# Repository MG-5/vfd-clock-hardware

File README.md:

# nixie-clock-hardware
Hardware for controlling six VFD IV-17 and two VFD IV-1 tubes as clock (HH:MM:SS) 

### Requirements for rev 1.0
* efficient step-boost converter up to 50V
* multiplexing
* control syncronous addressable LEDs
* PWM control
* I²C interface
* connector for ESP (UART)
* time syncronisation line for every second

### Known issues in rev 1.0
* octal buffer for PWM use seems do not works for dimming
  * workaround: dimming solved by adding turn-off points in mulitplexing routine (firmware-based solution)
* SPI is not suitable for controlling 20-bit shift register
  * cut traces and wire up to another pins

### Pictures (rev 1.0)

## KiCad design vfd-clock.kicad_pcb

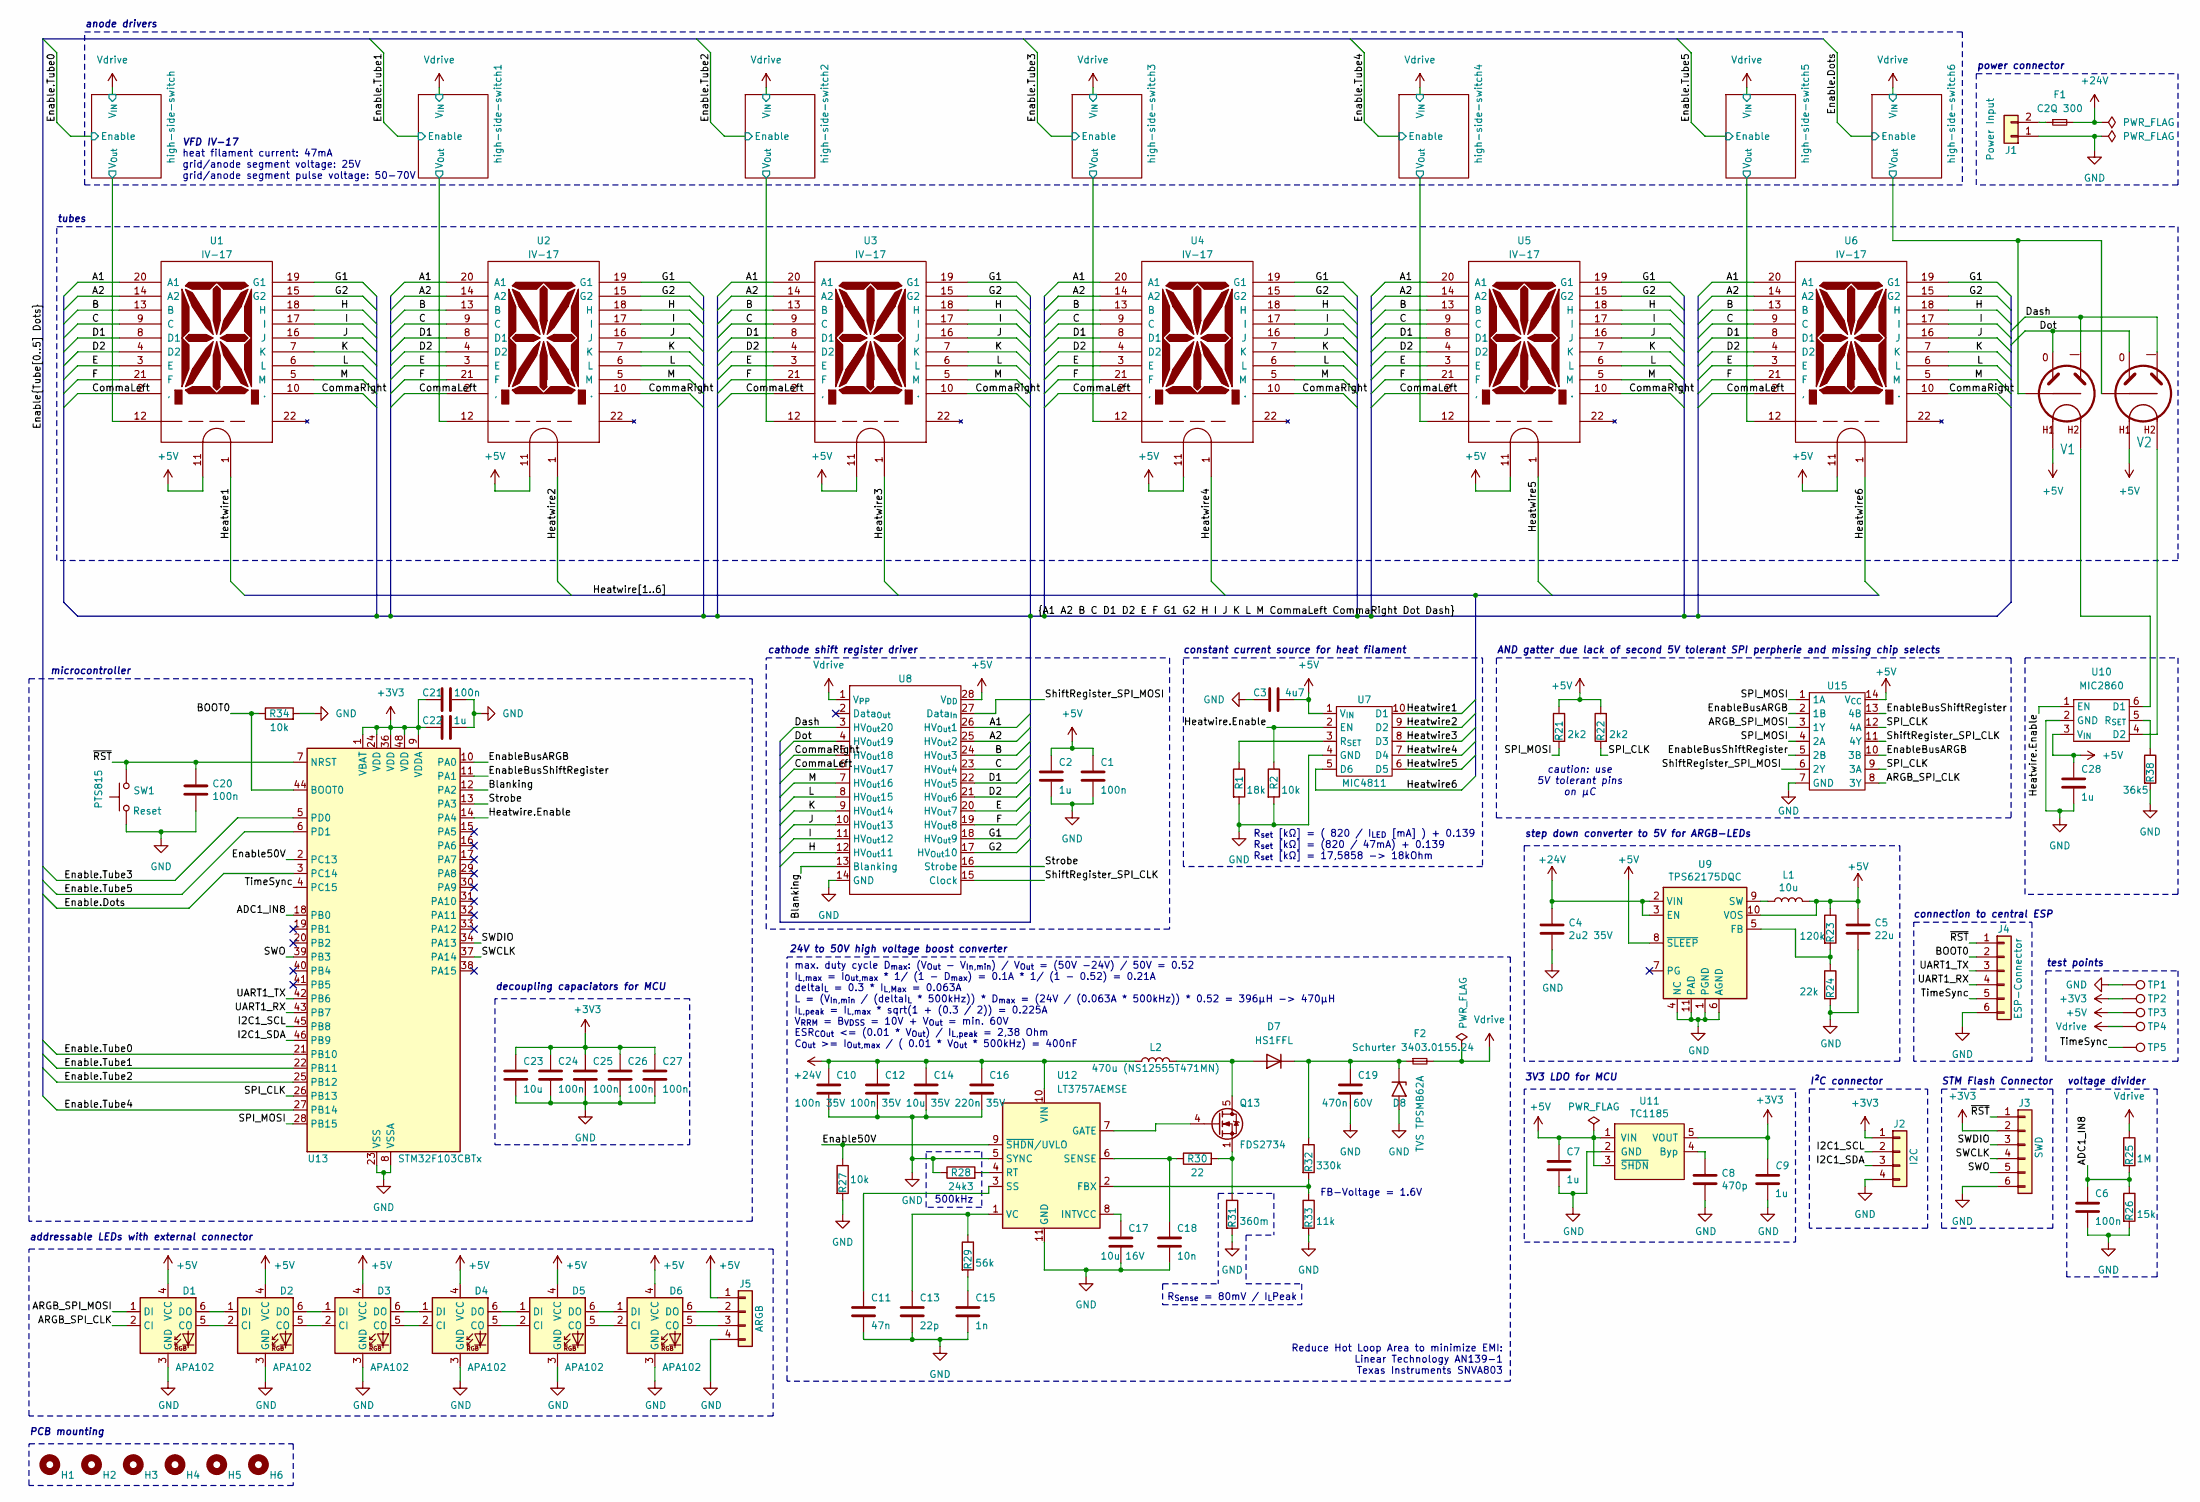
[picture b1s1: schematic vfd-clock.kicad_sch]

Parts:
C1, C6, C20, C21, C24, C25, C26, C27: 100n; C_0603_1608Metric_Pad1.08x0.95mm_HandSolder
C2, C7, C9, C22, C28: 1u; C_0805_2012Metric_Pad1.18x1.45mm_HandSolder
C3: 4u7; R_0603_1608Metric_Pad0.98x0.95mm_HandSolder
C4: 2u2 35V; C_0805_2012Metric_Pad1.18x1.45mm_HandSolder
C5: 22u; C_0805_2012Metric_Pad1.18x1.45mm_HandSolder
C8: 470p; C_0402_1005Metric_Pad0.74x0.62mm_HandSolder
C10, C12: 100n 35V; C_0603_1608Metric_Pad1.08x0.95mm_HandSolder
C11: 47n; C_0603_1608Metric_Pad1.08x0.95mm_HandSolder
C13: 22p; C_0402_1005Metric_Pad0.74x0.62mm_HandSolder
C14: 10u 35V; C_1206_3216Metric_Pad1.33x1.80mm_HandSolder
C15: 1n; C_0603_1608Metric_Pad1.08x0.95mm_HandSolder
C16: 220n 35V; C_0805_2012Metric_Pad1.18x1.45mm_HandSolder
C17: 10u 16V; C_0805_2012Metric_Pad1.18x1.45mm_HandSolder
C18: 10n; C_0603_1608Metric_Pad1.08x0.95mm_HandSolder
C19: 470n 60V; C_1206_3216Metric_Pad1.33x1.80mm_HandSolder
C23: 10u; C_0805_2012Metric_Pad1.18x1.45mm_HandSolder
D1, D2, D3, D4, D5, D6: APA102; LED_RGB_5050-6
D7: HS1FFL; D_SOD-123F
D8: TVS TPSMB62A; D_SMB_Handsoldering
F1: C2Q 300; Fuse_0603_1608Metric_Pad1.05x0.95mm_HandSolder
F2: Schurter 3403.0155.24; Fuse_Schurter_UMT250
H1, H2, H3, H4, H5, H6: MountingHole_Pad; MountingHole_3.2mm_M3_ISO14580
J1: Power Input; AMASS_XT30U-M_1x02_P5.0mm_Vertical
J2: I2C; Molex_PicoBlade_53047-0410_1x04_P1.25mm_Vertical
J3: SWD; Molex_PicoBlade_53047-0610_1x06_P1.25mm_Vertical
J4: ESP-Connector; Molex_PicoBlade_53047-0610_1x06_P1.25mm_Vertical
J5: ARGB; Molex_PicoBlade_53047-0410_1x04_P1.25mm_Vertical
L1: 10u; L_1210_3225Metric_Pad1.42x2.65mm_HandSolder
L2: 470u (NS12555T471MN); Taiyo Yuden NS 12.5mmx12.5mm
Q13: FDS2734; SOIC-8_3.9x4.9mm_P1.27mm
R1: 18k; R_0603_1608Metric_Pad0.98x0.95mm_HandSolder
R2, R27, R34: 10k; R_0603_1608Metric_Pad0.98x0.95mm_HandSolder
R21, R22: 2k2; R_0603_1608Metric_Pad0.98x0.95mm_HandSolder
R23: 120k; R_0603_1608Metric_Pad0.98x0.95mm_HandSolder
R24: 22k; R_0603_1608Metric_Pad0.98x0.95mm_HandSolder
R25: 1M; R_1206_3216Metric_Pad1.30x1.75mm_HandSolder
R26: 15k; R_0603_1608Metric_Pad0.98x0.95mm_HandSolder
R28: 24k3; R_0603_1608Metric_Pad0.98x0.95mm_HandSolder
R29: 56k; R_0603_1608Metric_Pad0.98x0.95mm_HandSolder
R30: 22; R_0603_1608Metric_Pad0.98x0.95mm_HandSolder
R31: 360m; R_0603_1608Metric_Pad0.98x0.95mm_HandSolder
R32: 330k; R_0603_1608Metric_Pad0.98x0.95mm_HandSolder
R33: 11k; R_0603_1608Metric_Pad0.98x0.95mm_HandSolder
R38: 36k5; R_0603_1608Metric_Pad0.98x0.95mm_HandSolder
SW1: PTS815; SW_SPST_PTS810
TP1: GND; TestPoint_THTPad_D1.5mm_Drill0.7mm
TP2: 3V3; TestPoint_THTPad_D1.5mm_Drill0.7mm
TP3: 5V; TestPoint_THTPad_D1.5mm_Drill0.7mm
TP4: 50V; TestPoint_THTPad_D1.5mm_Drill0.7mm
TP5: TimeSync; TestPoint_THTPad_D1.5mm_Drill0.7mm
U1, U2, U3, U4, U5, U6: IV-17
U7: MIC4811; MSOP-10_3x3mm_P0.5mm
U8: SOIC-28W_7.5x17.9mm_P1.27mm
U9: TPS62175DQC; WSON-10-1EP_2x3mm_P0.5mm_EP0.84x2.4mm_ThermalVias
U10: MIC2860; SOT-363_SC-70-6_Handsoldering
U11: TC1185; SOT-23-5
U12: LT3757AEMSE; MSOP-10-1EP_3x3mm_P0.5mm_EP1.68x1.88mm
U13: STM32F103CBTx; LQFP-48_7x7mm_P0.5mm
U15: SOIC-14_3.9x8.7mm_P1.27mm
V1, V2: mynixies-IV-1

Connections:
+3V3: C9.1, C21.2, C22.2, C23.1, C24.1, C25.1, C26.1, C27.1, J2.1, J3.2, TP2.1, U11.5 (VOUT), U13.1 (VBAT), U13.9 (VDDA), U13.24 (VDD), U13.36 (VDD), U13.48 (VDD)
+5V: C1.1, C2.1, C3.2, C5.1, C7.1, C28.1, D1.4 (VCC), D2.4 (VCC), D3.4 (VCC), D4.4 (VCC), D5.4 (VCC), D6.4 (VCC), J5.1, L1.2, R21.1, R22.1, R23.1, TP3.1, U1.11, U2.11, U3.11, U4.11, U5.11, U6.11, U7.1 (V_{IN}), U8.28 (V_{DD}), U9.8 (~SLEEP), U9.10 (VOS), U10.3 (V_{IN}), U11.1 (VIN), U11.3 (~SHDN), U15.14 (V_{CC}), V1.F1 (H1), V2.F1 (H1)
+24V: C4.1, C10.1, C12.1, C14.1, C16.1, F1.2, L2.1, U9.2 (VIN), U9.3 (EN), U12.10 (VIN)
/A1: U1.20 (A1), U2.20 (A1), U3.20 (A1), U4.20 (A1), U5.20 (A1), U6.20 (A1), U8.26 (HV_{Out}1)
/A2: U1.14 (A2), U2.14 (A2), U3.14 (A2), U4.14 (A2), U5.14 (A2), U6.14 (A2), U8.25 (HV_{Out}2)
/ADC1_IN8: C6.1, R25.2, R26.1, U13.18 (PB0)
/ARGB_SPI_CLK: D1.2 (CI), U15.8 (3Y)
/ARGB_SPI_MOSI: D1.1 (DI), U15.3 (1Y)
/B: U1.13 (B), U2.13 (B), U3.13 (B), U4.13 (B), U5.13 (B), U6.13 (B), U8.24 (HV_{Out}3)
/BOOT0: J4.2, R34.1, U13.44 (BOOT0)
/Blanking: U8.13 (Blanking), U13.12 (PA2)
/C: U1.9 (C), U2.9 (C), U3.9 (C), U4.9 (C), U5.9 (C), U6.9 (C), U8.23 (HV_{Out}4)
/CommaLeft: U1.2 (,), U2.2 (,), U3.2 (,), U4.2 (,), U5.2 (,), U6.2 (,), U8.6 (HV_{Out}17)
/CommaRight: U1.10 (.), U2.10 (.), U3.10 (.), U4.10 (.), U5.10 (.), U6.10 (.), U8.5 (HV_{Out}18)
/D1: U1.8 (D1), U2.8 (D1), U3.8 (D1), U4.8 (D1), U5.8 (D1), U6.8 (D1), U8.22 (HV_{Out}5)
/D2: U1.4 (D2), U2.4 (D2), U3.4 (D2), U4.4 (D2), U5.4 (D2), U6.4 (D2), U8.21 (HV_{Out}6)
/Dash: U8.3 (HV_{Out}20), V1.-, V2.-
/Dot: U8.4 (HV_{Out}19), V1.O, V2.O
/E: U1.3 (E), U2.3 (E), U3.3 (E), U4.3 (E), U5.3 (E), U6.3 (E), U8.20 (HV_{Out}7)
/Enable50V: R27.1, U12.9 (~SHDN/UVLO), U13.2 (PC13)
/Enable.Dots: U13.3 (PC14); also elsewhere on the board
/Enable.Tube0: U13.21 (PB10); also elsewhere on the board
/Enable.Tube1: U13.22 (PB11); also elsewhere on the board
/Enable.Tube2: U13.25 (PB12); also elsewhere on the board
/Enable.Tube3: U13.5 (PD0); also elsewhere on the board
/Enable.Tube4: U13.27 (PB14); also elsewhere on the board
/Enable.Tube5: U13.6 (PD1); also elsewhere on the board
/EnableBusARGB: U13.10 (PA0), U15.2 (1B), U15.10 (3B)
/EnableBusShiftRegister: U13.11 (PA1), U15.5 (2B), U15.13 (4B)
/F: U1.21 (F), U2.21 (F), U3.21 (F), U4.21 (F), U5.21 (F), U6.21 (F), U8.19 (HV_{Out}8)
/G1: U1.19 (G1), U2.19 (G1), U3.19 (G1), U4.19 (G1), U5.19 (G1), U6.19 (G1), U8.18 (HV_{Out}9)
/G2: U1.15 (G2), U2.15 (G2), U3.15 (G2), U4.15 (G2), U5.15 (G2), U6.15 (G2), U8.17 (HV_{Out}10)
/H: U1.18 (H), U2.18 (H), U3.18 (H), U4.18 (H), U5.18 (H), U6.18 (H), U8.12 (HV_{Out}11)
/Heatwire1: U1.1, U7.10 (D1)
/Heatwire2: U2.1, U7.9 (D2)
/Heatwire3: U3.1, U7.8 (D3)
/Heatwire4: U4.1, U7.7 (D4)
/Heatwire5: U5.1, U7.6 (D5)
/Heatwire6: U6.1, U7.5 (D6)
/Heatwire.Enable: R2.1, U7.2 (EN), U10.1 (EN), U13.14 (PA4)
/I: U1.17 (I), U2.17 (I), U3.17 (I), U4.17 (I), U5.17 (I), U6.17 (I), U8.11 (HV_{Out}12)
/I2C1_SCL: J2.2, U13.45 (PB8)
/I2C1_SDA: J2.3, U13.46 (PB9)
/J: U1.16 (J), U2.16 (J), U3.16 (J), U4.16 (J), U5.16 (J), U6.16 (J), U8.10 (HV_{Out}13)
/K: U1.7 (K), U2.7 (K), U3.7 (K), U4.7 (K), U5.7 (K), U6.7 (K), U8.9 (HV_{Out}14)
/L: U1.6 (L), U2.6 (L), U3.6 (L), U4.6 (L), U5.6 (L), U6.6 (L), U8.8 (HV_{Out}15)
/M: U1.5 (M), U2.5 (M), U3.5 (M), U4.5 (M), U5.5 (M), U6.5 (M), U8.7 (HV_{Out}16)
/SPI_CLK: R22.2, U13.26 (PB13), U15.9 (3A), U15.12 (4A)
/SPI_MOSI: R21.2, U13.28 (PB15), U15.1 (1A), U15.4 (2A)
/SWCLK: J3.4, U13.37 (PA14)
/SWDIO: J3.3, U13.34 (PA13)
/SWO: J3.5, U13.39 (PB3)
/ShiftRegister_SPI_CLK: U8.15 (Clock), U15.11 (4Y)
/ShiftRegister_SPI_MOSI: U8.27 (Data_{In}), U15.6 (2Y)
/Strobe: U8.16 (Strobe), U13.13 (PA3)
/TimeSync: J4.5, TP5.1, U13.4 (PC15)
/UART1_RX: J4.4, U13.43 (PB7)
/UART1_TX: J4.3, U13.42 (PB6)
/high-side-switch1/V_{Out}: U2.12; also elsewhere on the board
/high-side-switch2/V_{Out}: U3.12; also elsewhere on the board
/high-side-switch3/V_{Out}: U4.12; also elsewhere on the board
/high-side-switch4/V_{Out}: U5.12; also elsewhere on the board
/high-side-switch5/V_{Out}: U6.12; also elsewhere on the board
/high-side-switch6/V_{Out}: V1.G, V2.G; also elsewhere on the board
/high-side-switch/V_{Out}: U1.12; also elsewhere on the board
/~RST: C20.1, J3.1, J4.1, SW1.2, U13.7 (NRST)
GND: C1.2, C2.2, C3.1, C4.2, C5.2, C6.2, C7.2, C8.2, C9.2, C10.2, C11.2, C12.2, C13.2, C14.2, C15.2, C16.2, C17.2, C18.2, C19.2, C20.2, C21.1, C22.1, C23.2, C24.2, C25.2, C26.2, C27.2, C28.2, D1.3 (GND), D2.3 (GND), D3.3 (GND), D4.3 (GND), D5.3 (GND), D6.3 (GND), D8.2 (A2), J1.1, J2.4, J3.6, J4.6, J5.4, R1.2, R2.2, R24.2, R26.2, R27.2, R28.1, R31.2, R33.2, R34.2, R38.2, SW1.1, TP1.1, U7.4 (GND), U8.14 (GND), U9.1 (PGND), U9.4 (NC), U9.6 (AGND), U9.11 (PAD), U10.2 (GND), U11.2 (GND), U12.5 (SYNC), U12.11 (GND), U13.8 (VSSA), U13.23 (VSS), U13.35 (VSS), U13.47 (VSS), U15.7 (GND); also elsewhere on the board
unnamed: C15.1, R29.2
unnamed: D1.5 (CO), D2.2 (CI)
unnamed: D1.6 (DO), D2.1 (DI)
unnamed: D2.5 (CO), D3.2 (CI)
unnamed: D2.6 (DO), D3.1 (DI)
unnamed: D3.5 (CO), D4.2 (CI)
unnamed: D3.6 (DO), D4.1 (DI)
unnamed: D4.5 (CO), D5.2 (CI)
unnamed: D4.6 (DO), D5.1 (DI)
unnamed: D5.5 (CO), D6.2 (CI)
unnamed: D5.6 (DO), D6.1 (DI)
unnamed: D6.5 (CO), J5.3
unnamed: D6.6 (DO), J5.2
unnamed: D7.2 (A), L2.2, Q13.5 (D), Q13.6 (D), Q13.7 (D), Q13.8 (D)
unnamed: C19.1, D7.1 (K), D8.1 (A1), F2.1, R32.1
unnamed: F1.1, J1.2
unnamed: Q13.4 (G), U12.7 (GATE)
unnamed: Q13.1 (S), Q13.2 (S), Q13.3 (S), R30.2, R31.1
unnamed: R1.1, U7.3 (R_{SET})
unnamed: R23.2, R24.1, U9.5 (FB)
unnamed: L1.1, U9.9 (SW)
unnamed: U10.6 (D1), V1.F2 (H2)
unnamed: U10.4 (D2), V2.F2 (H2)
unnamed: R38.1, U10.5 (R_{SET})
unnamed: C8.1, U11.4 (Byp)
unnamed: R32.2, R33.1, U12.2 (FBX)
unnamed: C17.1, U12.8 (INTVCC)
unnamed: R28.2, U12.4 (RT)
unnamed: C18.1, R30.1, U12.6 (SENSE)
unnamed: C11.1, U12.3 (SS)
unnamed: C13.1, R29.1, U12.1 (VC)
Vdrive: F2.2, R25.1, TP4.1, U8.1 (V_{PP}); also elsewhere on the board

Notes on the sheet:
voltage divider
anode drivers
24V to 50V high voltage boost converter
R_{set} [kΩ] = ( 820 / I_{LED} [mA] ) + 0.139 R_{set} [kΩ] = (820 / 47mA) + 0.139 R_{set} [kΩ] = 17,5858 -> 18kOhm
cathode shift register driver
FB-Voltage = 1.6V
step down converter to 5V for ARGB-LEDs
connection to central ESP
VFD IV-17
Reduce Hot Loop Area to minimize EMI: Linear Technology AN139-1 Texas Instruments SNVA803
microcontroller
3V3 LDO for MCU
500kHz
addressable LEDs with external connector
PCB mounting
max. duty cycle D_{max}: (V_{Out} - V_{In,min}) / V_{Out} = (50V -24V) / 50V = 0.52 I_{L,max} = I_{Out,max} * 1/ (1 - D_{max}) = 0.1A * 1/ (1 - 0.52) = 0.21A deltaI_{L} = 0.3 * I_{L,Max} = 0.063A L = (V_{In,min} / (deltaI_{L} * 500kHz)) * D_{max} = (24V / (0.063A * 500kHz)) * 0.52 = 396µH -> 470µH 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
heat filament current: 47mA grid/anode segment voltage: 25V grid/anode segment pulse voltage: 50-70V
constant current source for heat filament
R_{Sense} = 80mV / I_{L}Peak
decoupling capaciators for MCU
I²C connector
power connector
test points
AND gatter due lack of second 5V tolerant SPI perpherie and missing chip selects
caution: use 5V tolerant pins on µC
tubes
STM Flash Connector

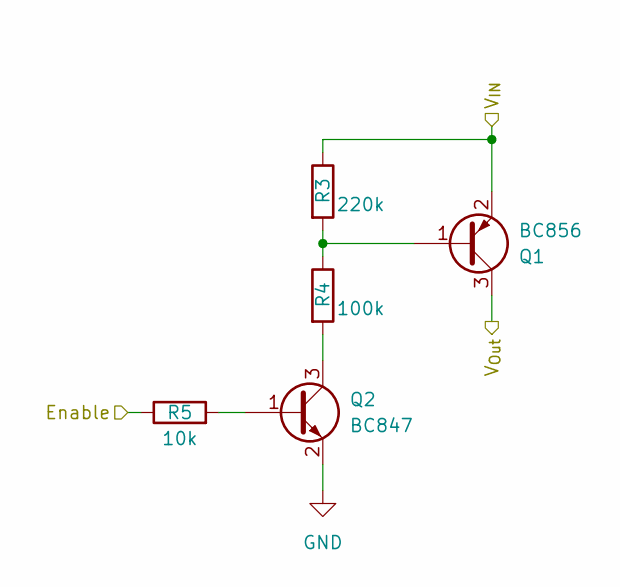
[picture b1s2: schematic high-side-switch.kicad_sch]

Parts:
Q1: BC856; SOT-23
Q2: BC847; SOT-23
R3: 220k; R_0603_1608Metric_Pad0.98x0.95mm_HandSolder
R4: 100k; R_0603_1608Metric_Pad0.98x0.95mm_HandSolder
R5: 10k; R_0603_1608Metric_Pad0.98x0.95mm_HandSolder

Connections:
/Enable.Tube0: R5.1; also elsewhere on the board
/high-side-switch/V_{Out}: Q1.3 (C); also elsewhere on the board
GND: Q2.2 (E); also elsewhere on the board
unnamed: Q1.1 (B), R3.2, R4.1
unnamed: Q2.1 (B), R5.2
unnamed: Q2.3 (C), R4.2
Vdrive: Q1.2 (E), R3.1; also elsewhere on the board

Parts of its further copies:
Q3, Q5, Q7, Q9, Q11, Q14: BC847; SOT-23
Q4, Q6, Q8, Q10, Q12, Q15: BC856; SOT-23
R6, R9, R12, R15, R18, R35: 10k; R_0603_1608Metric_Pad0.98x0.95mm_HandSolder
R7, R10, R13, R16, R19, R36: 220k; R_0603_1608Metric_Pad0.98x0.95mm_HandSolder
R8, R11, R14, R17, R20, R37: 100k; R_0603_1608Metric_Pad0.98x0.95mm_HandSolder

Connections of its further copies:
/Enable.Dots: R35.1; also elsewhere on the board
/Enable.Tube1: R6.1; also elsewhere on the board
/Enable.Tube2: R9.1; also elsewhere on the board
/Enable.Tube3: R12.1; also elsewhere on the board
/Enable.Tube4: R15.1; also elsewhere on the board
/Enable.Tube5: R18.1; also elsewhere on the board
/high-side-switch1/V_{Out}: Q4.3 (C); also elsewhere on the board
/high-side-switch2/V_{Out}: Q6.3 (C); also elsewhere on the board
/high-side-switch3/V_{Out}: Q8.3 (C); also elsewhere on the board
/high-side-switch4/V_{Out}: Q10.3 (C); also elsewhere on the board
/high-side-switch5/V_{Out}: Q12.3 (C); also elsewhere on the board
/high-side-switch6/V_{Out}: Q15.3 (C); also elsewhere on the board
GND: Q3.2 (E), Q5.2 (E), Q7.2 (E), Q9.2 (E), Q11.2 (E), Q14.2 (E); also elsewhere on the board
unnamed: Q3.1 (B), R6.2
unnamed: Q3.3 (C), R8.2
unnamed: Q4.1 (B), R7.2, R8.1
unnamed: Q5.1 (B), R9.2
unnamed: Q5.3 (C), R11.2
unnamed: Q6.1 (B), R10.2, R11.1
unnamed: Q7.1 (B), R12.2
unnamed: Q7.3 (C), R14.2
unnamed: Q8.1 (B), R13.2, R14.1
unnamed: Q9.1 (B), R15.2
unnamed: Q9.3 (C), R17.2
unnamed: Q10.1 (B), R16.2, R17.1
unnamed: Q11.1 (B), R18.2
unnamed: Q11.3 (C), R20.2
unnamed: Q12.1 (B), R19.2, R20.1
unnamed: Q14.1 (B), R35.2
unnamed: Q14.3 (C), R37.2
unnamed: Q15.1 (B), R36.2, R37.1
Vdrive: Q4.2 (E), Q6.2 (E), Q8.2 (E), Q10.2 (E), Q12.2 (E), Q15.2 (E), R7.1, R10.1, R13.1, R16.1, R19.1, R36.1; also elsewhere on the board

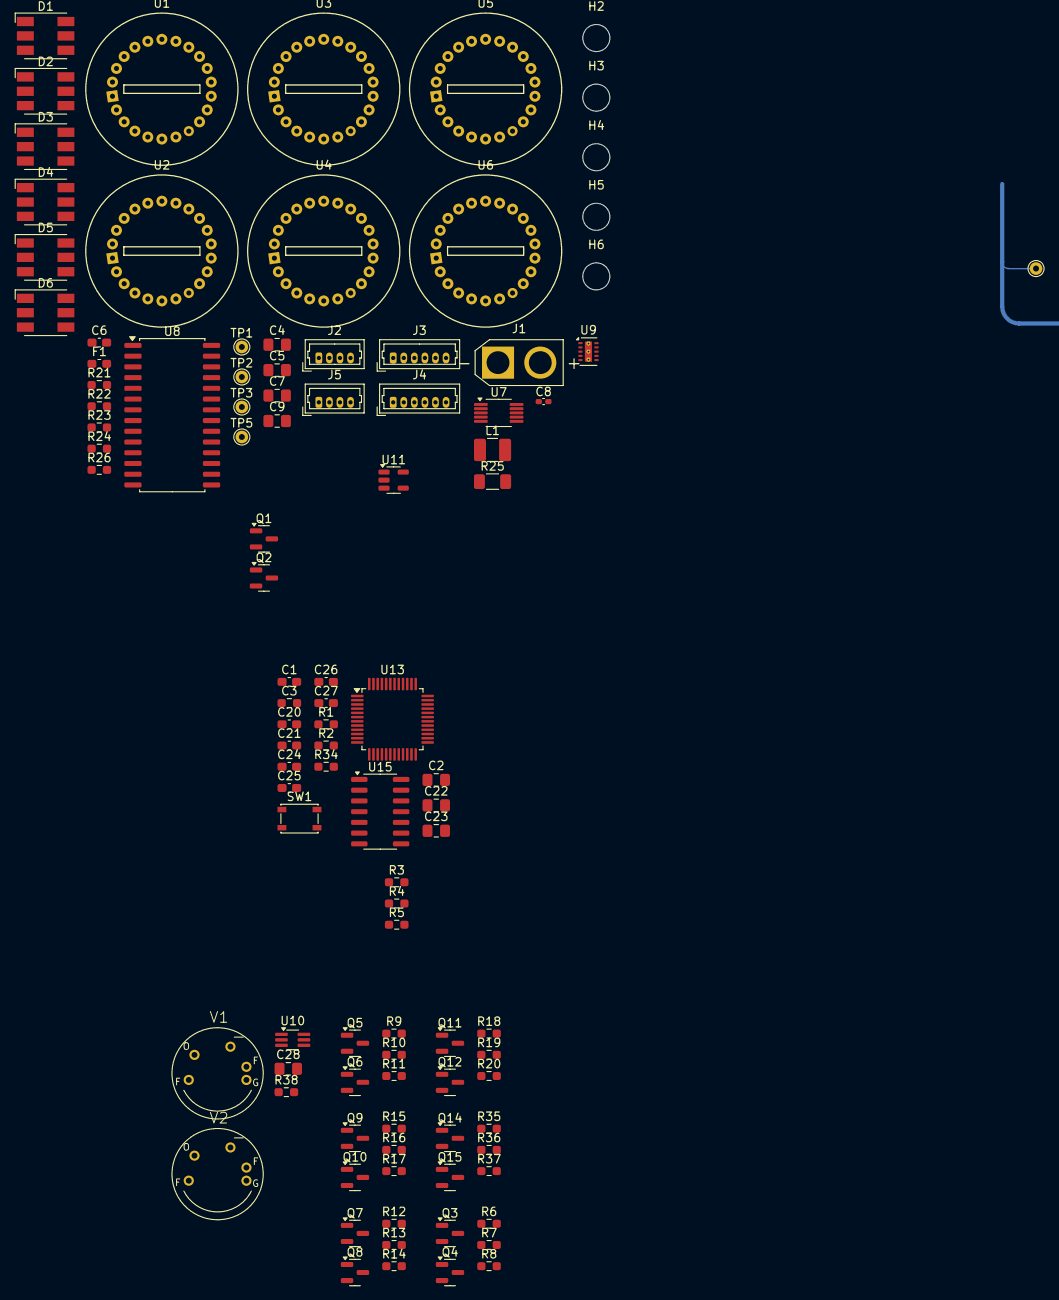
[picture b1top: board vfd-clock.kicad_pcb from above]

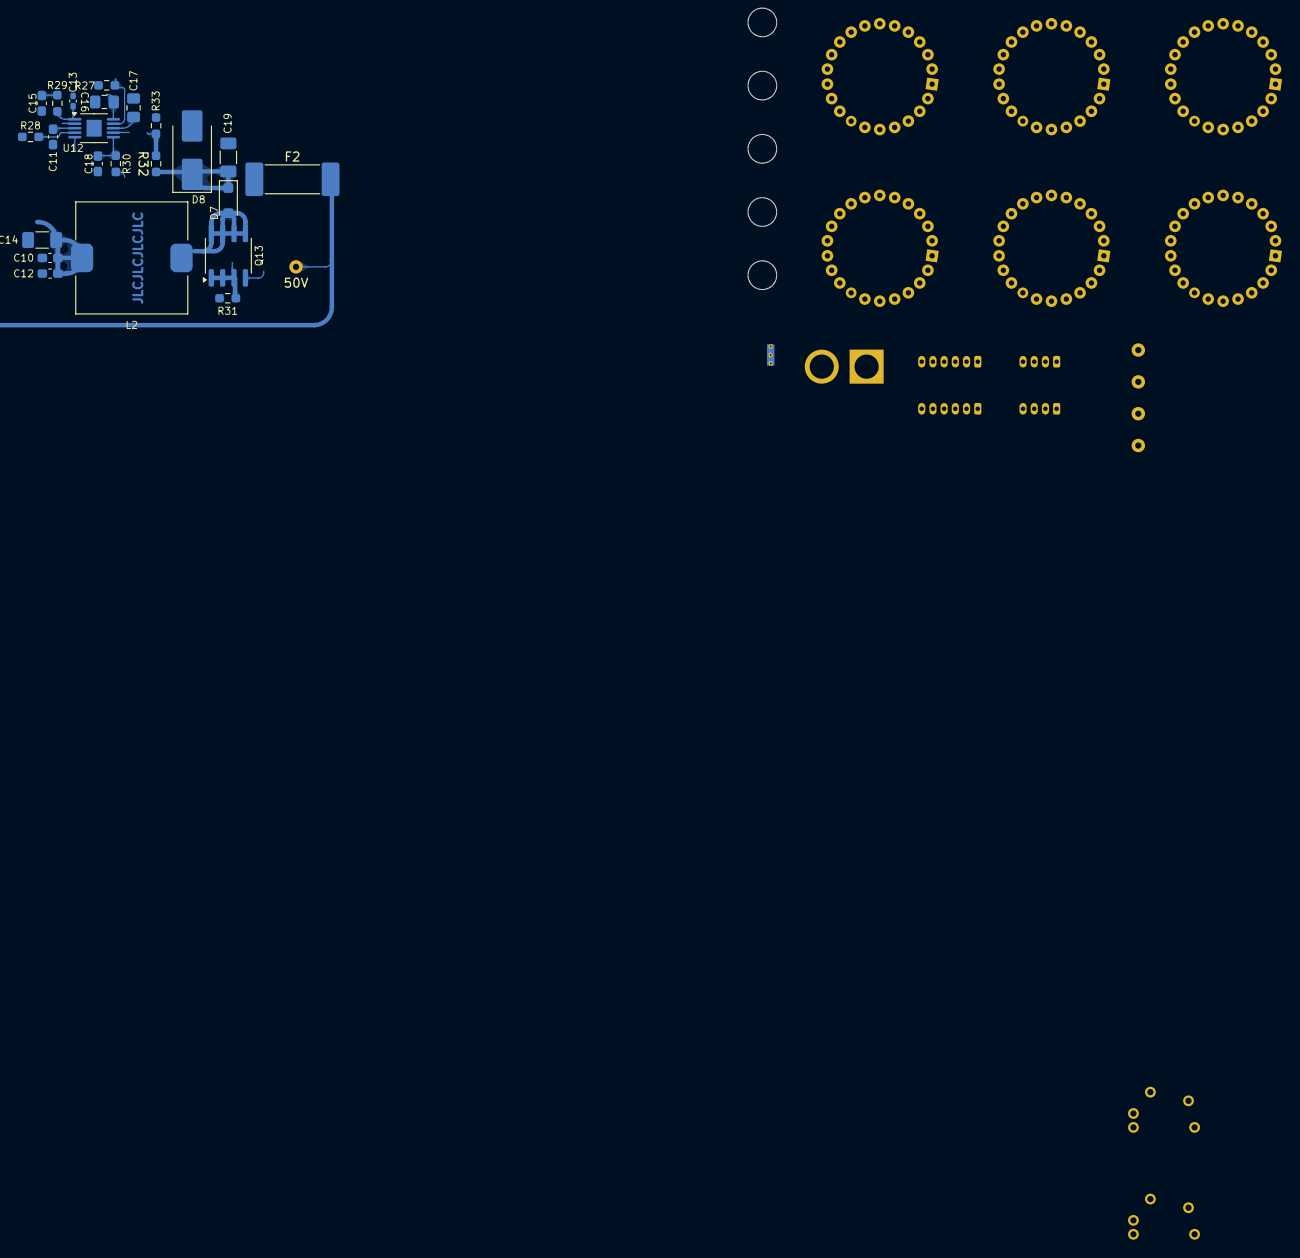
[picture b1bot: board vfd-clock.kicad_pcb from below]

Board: 2 copper layers, 126 parts (23 on the bottom side), 120 nets.

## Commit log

2024-03-18 Init KiCad project
2024-03-18 Add submodule containing IV-17
2024-03-21 [WIP] Add schematic and submodule for IV-1
2024-04-04 Add schematic, submodule for IV-1 and PCB
2024-04-07 Final workings
2024-04-07 Create LICENSE
2024-06-13 Add ReadMe and a note to schematic
2024-06-13 Add LTSpice simulation
2024-12-29 Add images of assembled clock to ReadMe
